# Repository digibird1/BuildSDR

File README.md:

BuildSDR
========

Drawings and code to build a own Software Defined Radio

Drawings for the ERA-3SM+ amplifier, the NXP SA612A mixer, and an OpAmp driver for the ADC

Flow graph for GNU Radio

VHDL source code to read the ADC and do USB communication... basically the same as in the USB ADC FPGA project

For a detailed description see:
http://digibird1.wordpress.com

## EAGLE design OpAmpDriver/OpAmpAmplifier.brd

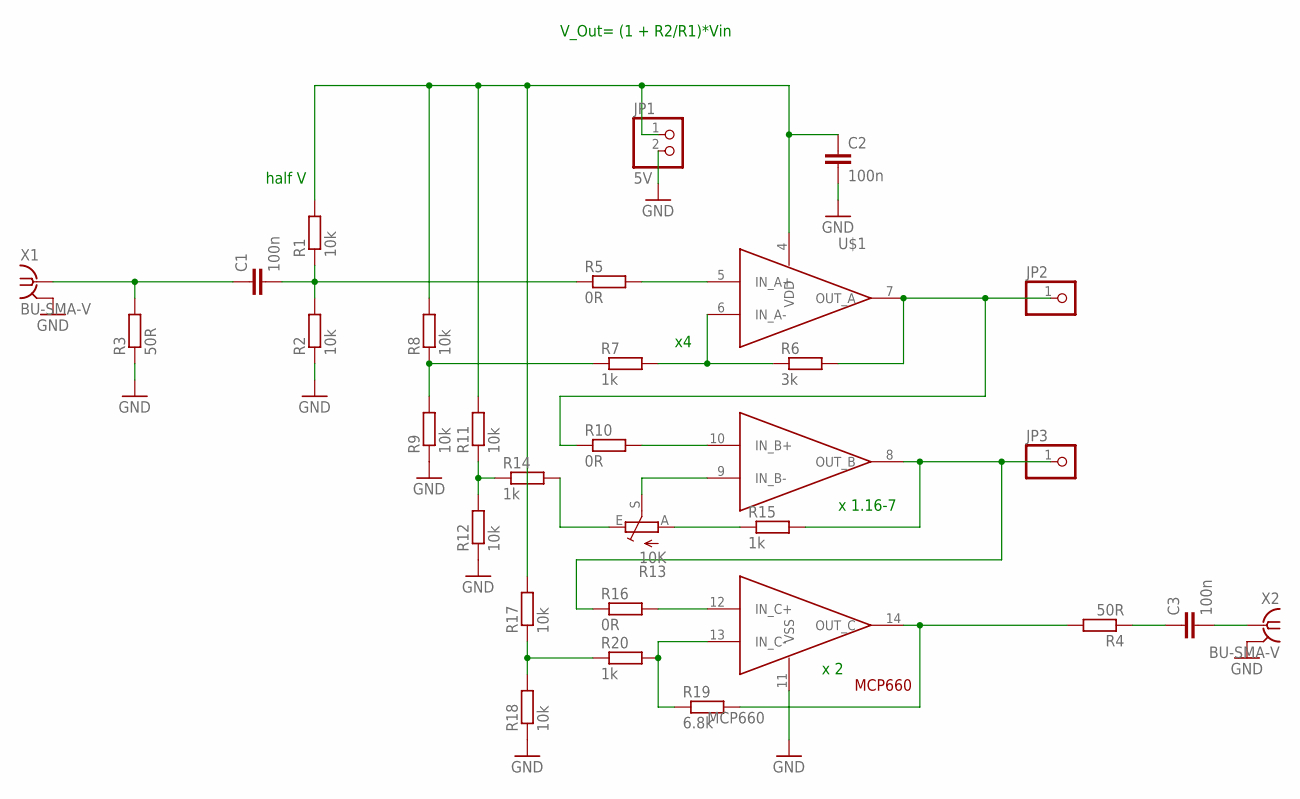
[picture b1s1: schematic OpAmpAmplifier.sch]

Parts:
C1, C2, C3: 100n; C0805
JP1: 5V; 1X02
JP2, JP3: PINHD-1X1; 1X01
R1, R2, R8, R9, R11, R12, R17, R18: 10k; R0805
R3, R4: 50R; R0805
R5, R10, R16: 0R; R0805
R6: 3k; R0805
R7, R14, R15, R20: 1k; R0805
R13: 10K; CA6V
R19: 6.8k; R0805
U$1: MCP660; SO14
X1, X2: BU-SMA-V

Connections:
GND: C2.2, JP1.2, R2.1, R3.1, R9.1, R12.1, R18.1, U$1.11 (VSS), X1.2, X1.3 (2), X1.4 (2), X1.5 (2), X2.2, X2.3 (2), X2.4 (2), X2.5 (2)
unnamed: C2.1, JP1.1, R1.2, R8.2, R11.2, R17.2, U$1.4 (VDD)
unnamed: C1.1, R3.2, X1.1
unnamed: C1.2, R1.1, R2.2, R5.1
unnamed: R10.2, U$1.10 (IN_B+)
unnamed: C3.1, R4.1
unnamed: C3.2, X2.1
unnamed: R5.2, U$1.5 (IN_A+)
unnamed: JP2.1, R6.2, R10.1, U$1.7 (OUT_A)
unnamed: R6.1, R7.2, U$1.6 (IN_A-)
unnamed: R7.1, R8.1, R9.2
unnamed: R11.1, R12.2, R14.1
unnamed: R13.E, R14.2
unnamed: JP3.1, R15.2, R16.1, U$1.8 (OUT_B)
unnamed: R13.S, U$1.9 (IN_B-)
unnamed: R13.A, R15.1
unnamed: R16.2, U$1.12 (IN_C+)
unnamed: R17.1, R18.2, R20.1
unnamed: R4.2, R19.2, U$1.14 (OUT_C)
unnamed: R19.1, R20.2, U$1.13 (IN_C-)

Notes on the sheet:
half V
V_Out= (1 + R2/R1)*Vin
x 1.16-7
x 2

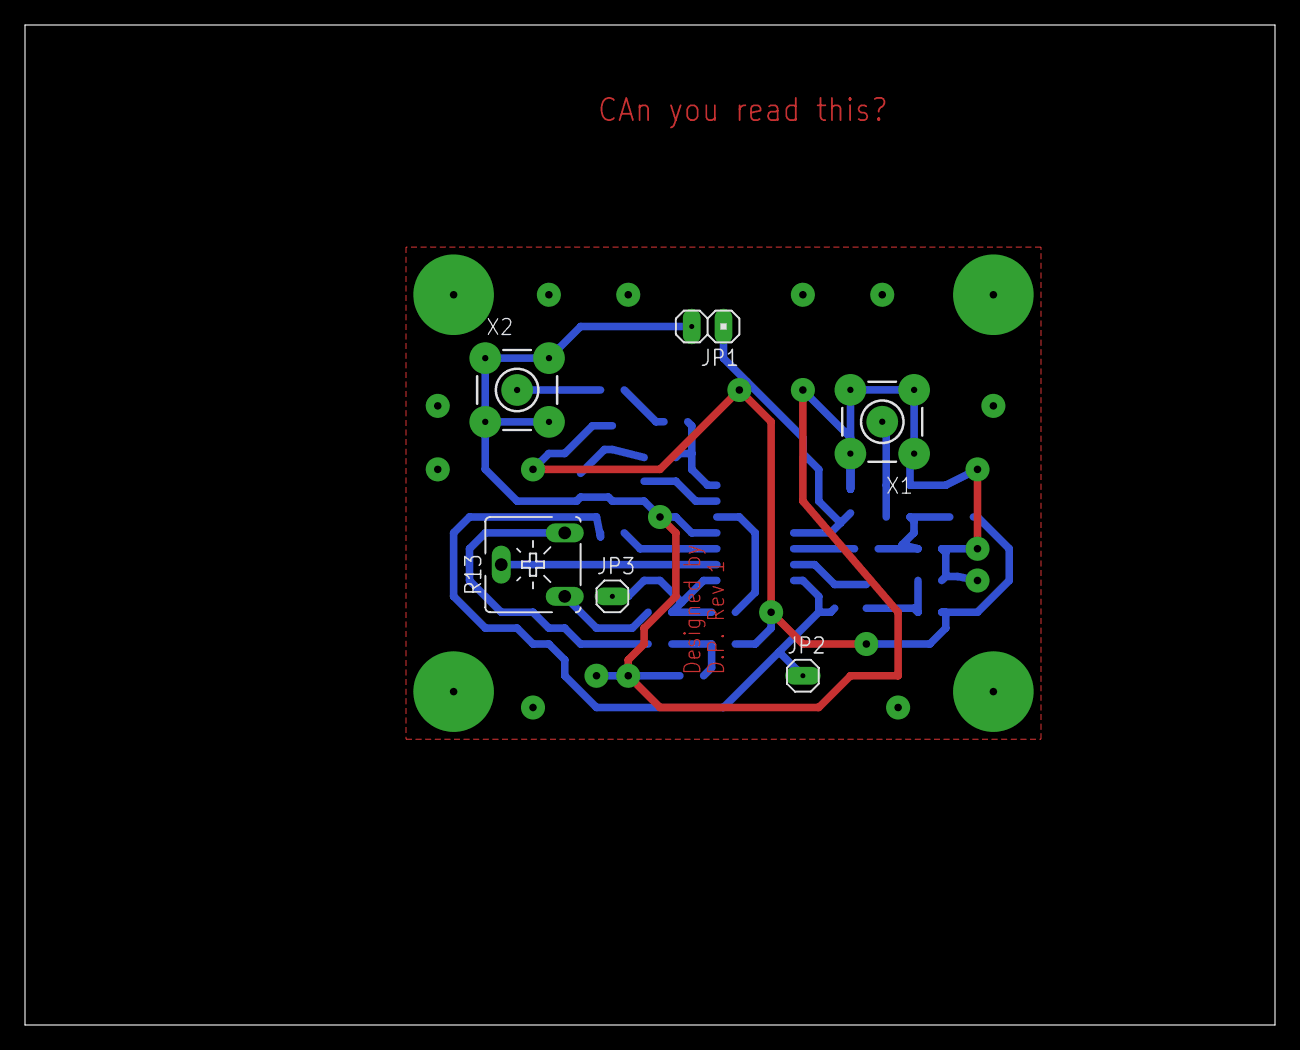
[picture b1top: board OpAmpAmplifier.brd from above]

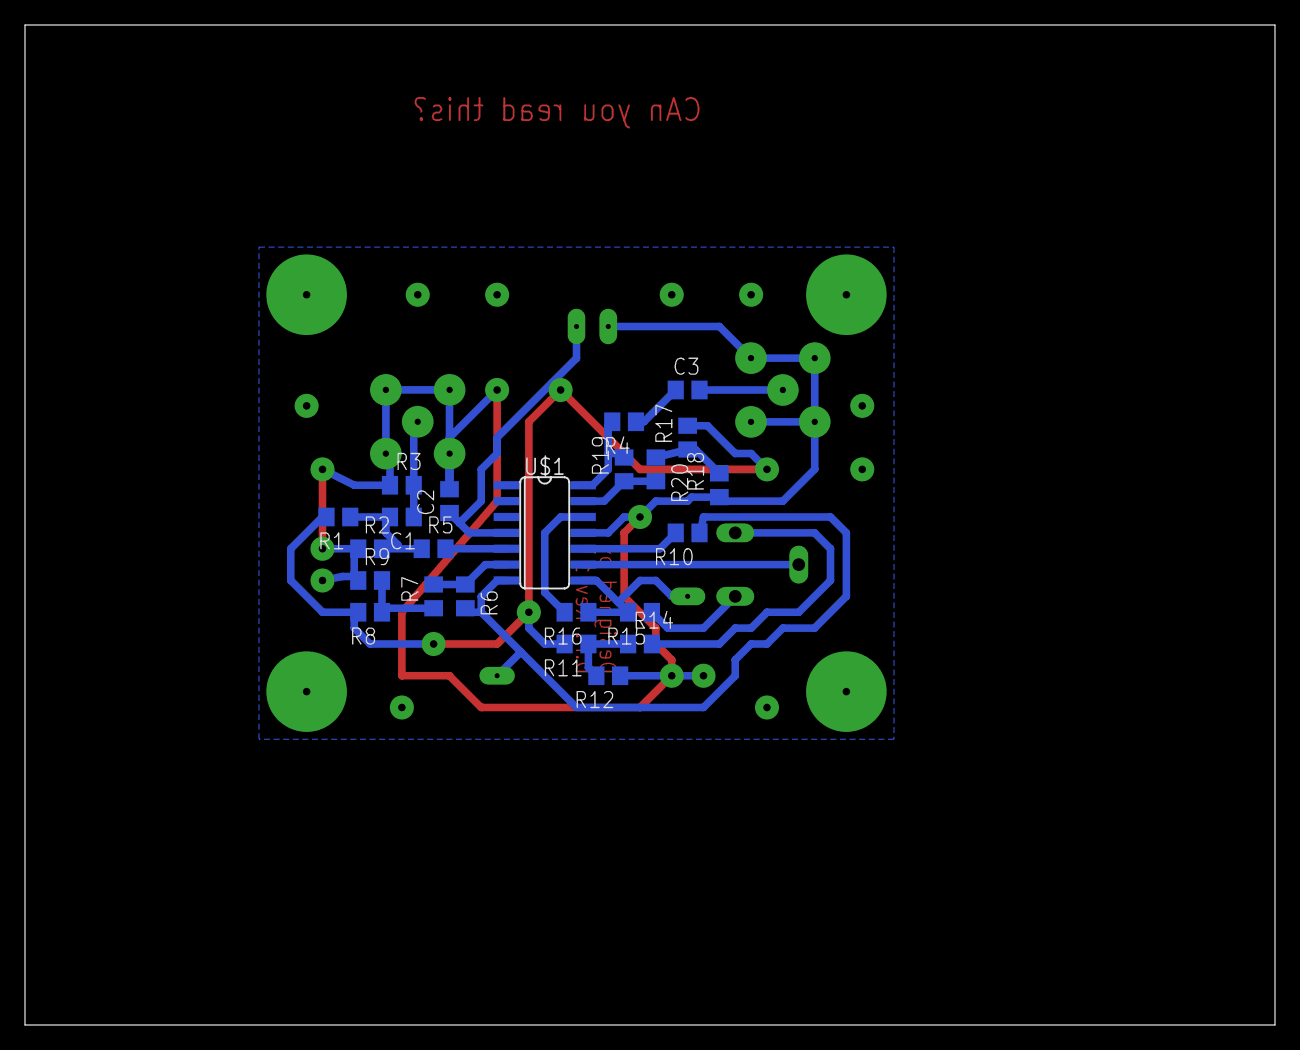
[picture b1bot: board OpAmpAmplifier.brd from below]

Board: 2 copper layers, 100.0 x 80.0 mm, 29 parts (23 on the bottom side), 20 nets.

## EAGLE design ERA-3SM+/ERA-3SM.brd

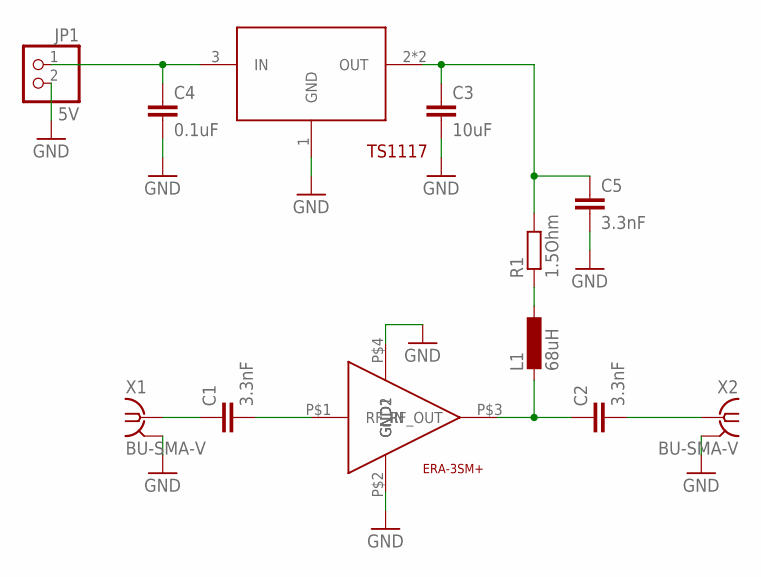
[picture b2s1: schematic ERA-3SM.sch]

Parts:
C1, C2, C5: 3.3nF; C0805
C3: 10uF; C0805
C4: 0.1uF; C0805
JP1: 5V; 1X02
L1: 68uH; 1616FPS
R1: 1.5Ohm; R0805
U$1: ERA-3SM+; WW107
U$2: TS1117; SOT223
X1, X2: BU-SMA-V

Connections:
GND: C3.2, C4.2, C5.2, JP1.2, U$1.P$2 (GND1), U$1.P$4 (GND2), U$2.1 (GND), X1.2, X1.3 (2), X1.4 (2), X1.5 (2), X2.2, X2.3 (2), X2.4 (2), X2.5 (2)
unnamed: C1.1, X1.1
unnamed: C1.2, U$1.P$1 (RF_IN)
unnamed: C2.1, L1.P$2 (2), U$1.P$3 (RF_OUT)
unnamed: C2.2, X2.1
unnamed: L1.P$1 (1), R1.1
unnamed: C3.1, C5.1, R1.2, U$2.2 (OUT), U$2.4 (OUT)
unnamed: C4.1, JP1.1, U$2.3 (IN)

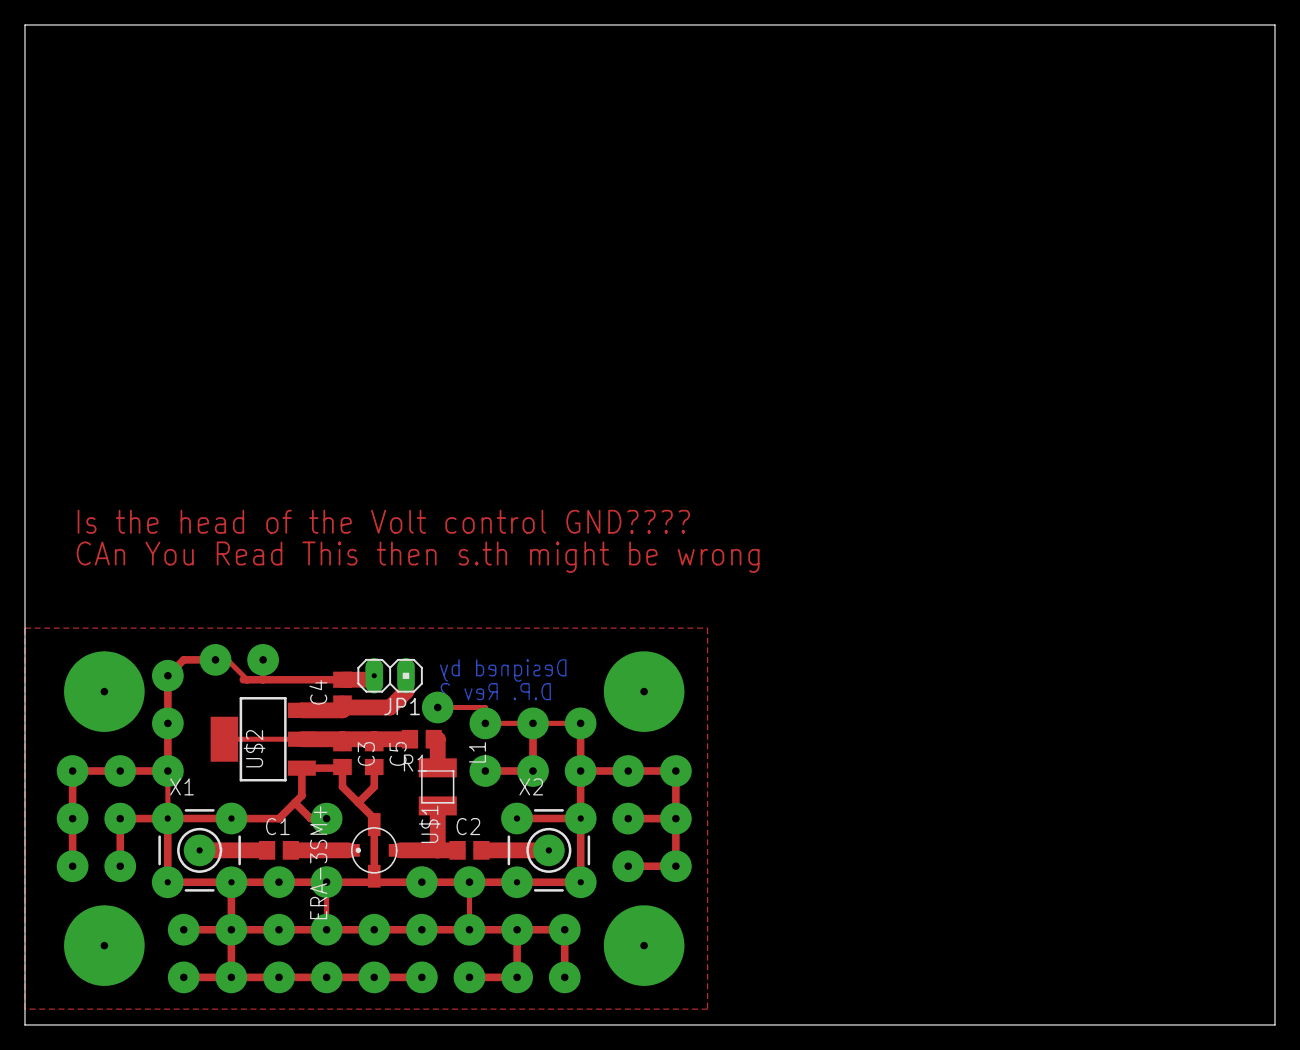
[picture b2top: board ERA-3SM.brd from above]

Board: 2 copper layers, 100.0 x 80.0 mm, 12 parts (0 on the bottom side), 8 nets.

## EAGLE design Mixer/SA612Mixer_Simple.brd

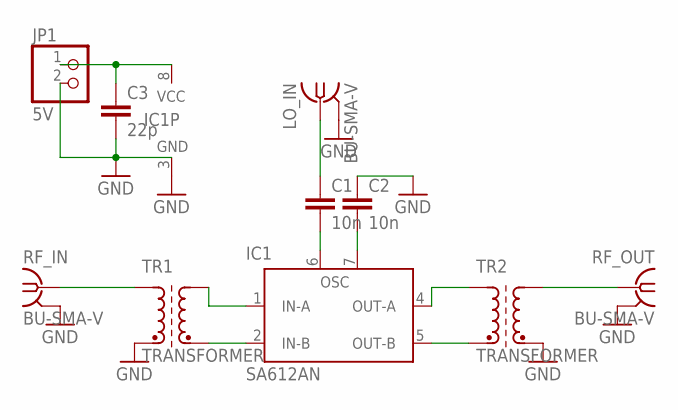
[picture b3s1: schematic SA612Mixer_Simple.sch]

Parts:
C1, C2: 10n; C5B2.5
C3: 22p; C5B2.5
IC1: SA612AN; DIL08
JP1: 5V; 1X02
LO_IN: BU-SMA-V
RF_IN: BU-SMA-V
RF_OUT: BU-SMA-V
TR1, TR2: TRANSFORMER; TRANSFORMER1

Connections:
GND: C2.1, C3.2, IC1.3 (GND), JP1.2, LO_IN.2, LO_IN.3 (2), LO_IN.4 (2), LO_IN.5 (2), RF_IN.2, RF_IN.3 (2), RF_IN.4 (2), RF_IN.5 (2), RF_OUT.2, RF_OUT.3 (2), RF_OUT.4 (2), RF_OUT.5 (2), TR1.P$2 (E1), TR2.P$4 (E2)
unnamed: C3.1, IC1.8 (VCC), JP1.1
unnamed: C1.2, IC1.6 (OSC)
unnamed: C1.1, LO_IN.1
unnamed: C2.2, IC1.7 (OSC')
unnamed: IC1.2 (IN-B), TR1.P$4 (E2)
unnamed: IC1.1 (IN-A), TR1.P$3 (A2)
unnamed: IC1.4 (OUT-A), TR2.P$1 (A1)
unnamed: IC1.5 (OUT-B), TR2.P$2 (E1)
unnamed: RF_IN.1, TR1.P$1 (A1)
unnamed: RF_OUT.1, TR2.P$3 (A2)

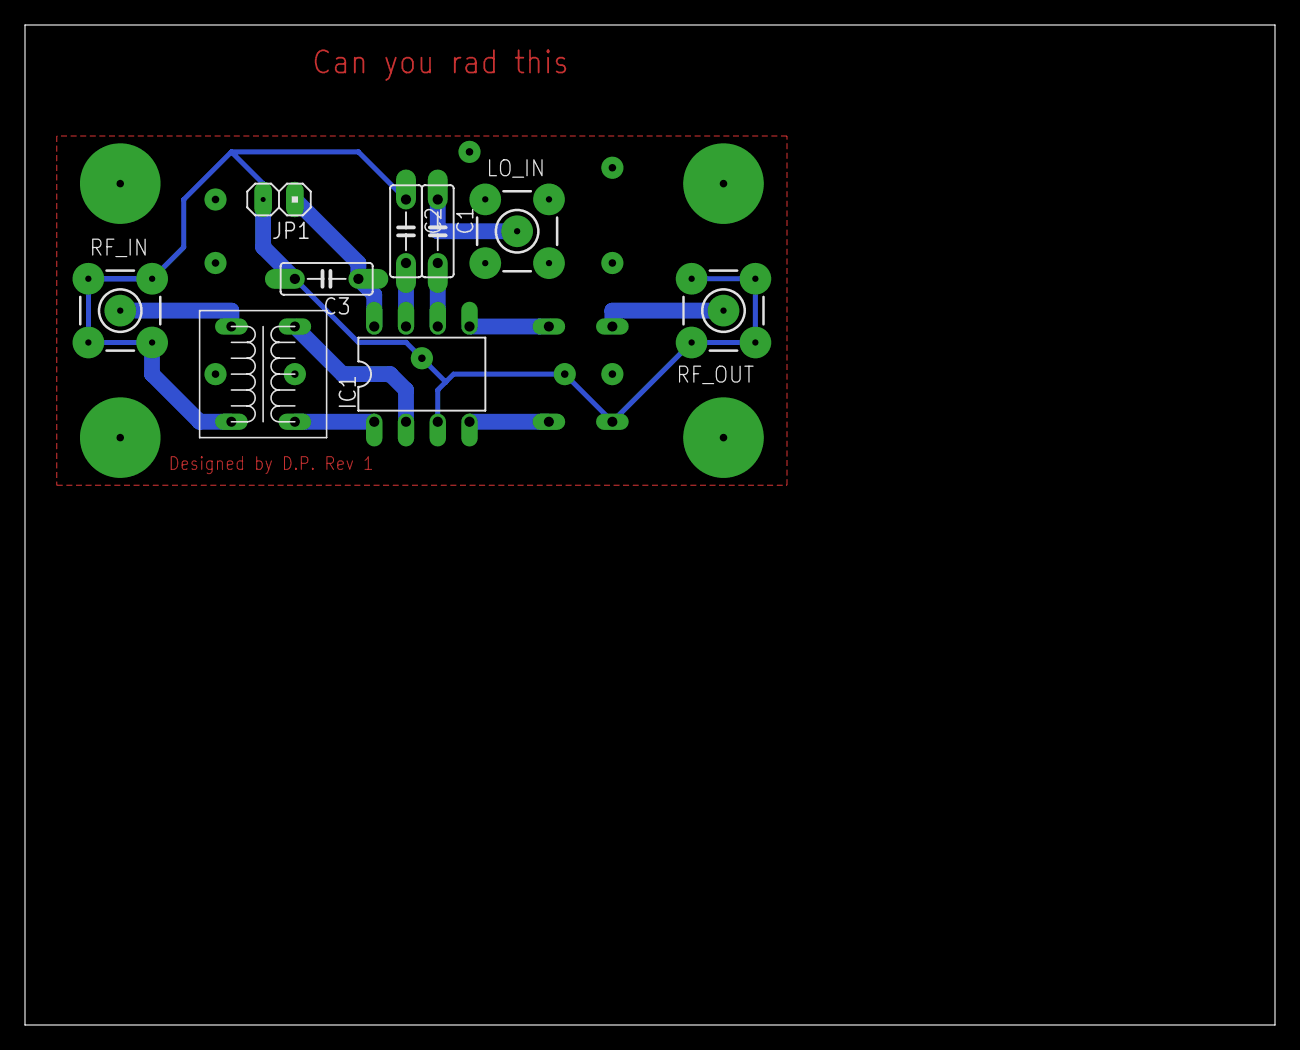
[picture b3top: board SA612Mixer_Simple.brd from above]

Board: 2 copper layers, 100.0 x 80.0 mm, 10 parts (1 on the bottom side), 11 nets.

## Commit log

2014-10-09 First check in
2014-10-09 Change ReadMe
